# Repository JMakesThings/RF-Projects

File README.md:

RF projects span:
Wilkinson Power Dividers;
Switches (SPST, SPDT, pin diode, Active FET);
Transmission Lines;
Low Noise Amplifiers;
Transceiver Architectures;
Mixers;
Analysis of passive devices;
Oscillators;
Phase Locked Loops;
Power Amplifiers ;
and much more... ;

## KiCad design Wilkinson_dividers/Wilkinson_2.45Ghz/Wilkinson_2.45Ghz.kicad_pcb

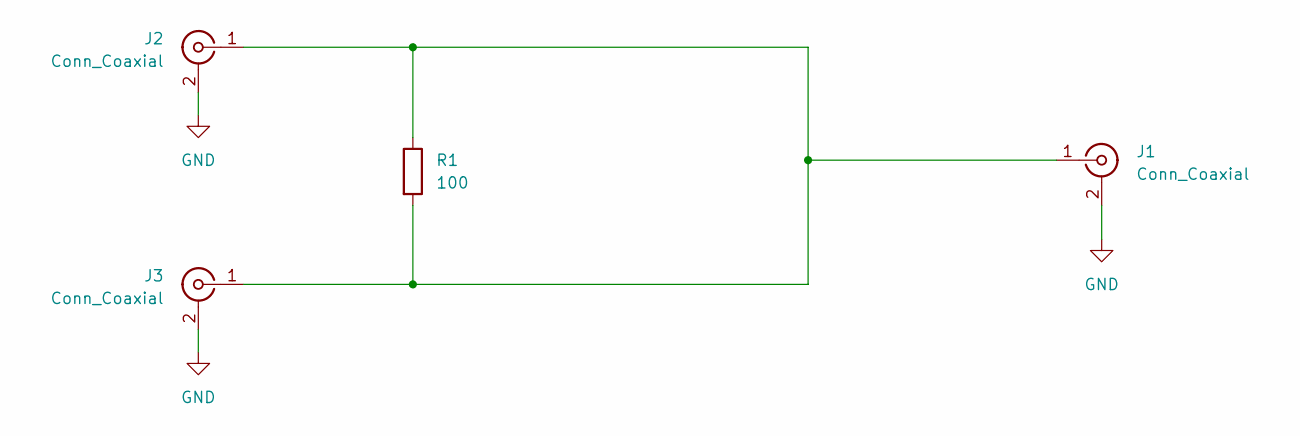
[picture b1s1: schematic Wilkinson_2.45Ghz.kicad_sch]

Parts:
J1, J2, J3: Conn_Coaxial; SMA_Amphenol_132289_EdgeMount
R1: 100; R_0402_1005Metric_Pad0.72x0.64mm_HandSolder

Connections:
GND: J1.2 (Ext), J2.2 (Ext), J3.2 (Ext)
unnamed: J1.1 (In), J2.1 (In), J3.1 (In), R1.1, R1.2

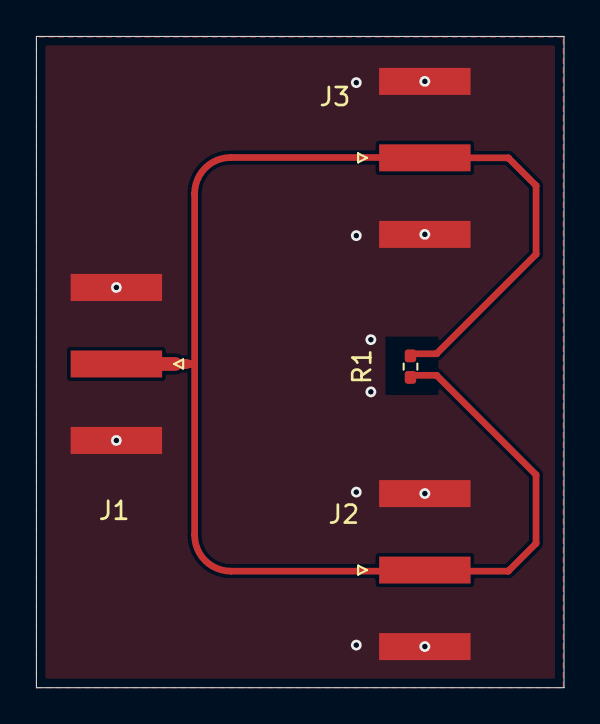
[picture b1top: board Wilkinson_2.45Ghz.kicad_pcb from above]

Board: 2 copper layers, 29.3 x 36.2 mm, 4 parts (0 on the bottom side), 2 nets.

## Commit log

2025-09-03 Adding Wilkinson divider 2.45GHz
2025-09-03 removed backups
2025-09-03 removed the fp info cache
